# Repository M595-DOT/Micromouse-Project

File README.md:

# Micromouse-Project NGCMAN017 & MDLAYA022

# Description
This project is for the development and design of a MicroMouse for EEE3088F 2025. The Micro Mouse contains a Sensing Module, Power Module, as well as the main control unit(Motherboard). The sensing system will sense obstacles in the proximity of the mouse, while the power module is mainly for powering the motors of the mouse and charging the on-board battery of the mouse.

# Structure
* PCB: The KiCAD Project, Schematics & Layout and Project Libraries
* Firmware: Any software developed for the hardware or instructions on where to find relevant sofware
* Documents: Project documentation and component datasheets
* Production: The gerber files, BOM, Budget, or anything required by the fabrication houses
* Simulation: Any simulation files (eg SPICE) or design stage generated results (E.g matlab or excel)

# Usage
The project documentation can be found in the Documents directory and the files required to produce the PCB can be found in the Production directory.

# Contact
* Manelisi Ngcobo - NGCMAN017@myuct.ac.za
* Ayanda Madlala  -MDLAYA022@myuct.ac.za

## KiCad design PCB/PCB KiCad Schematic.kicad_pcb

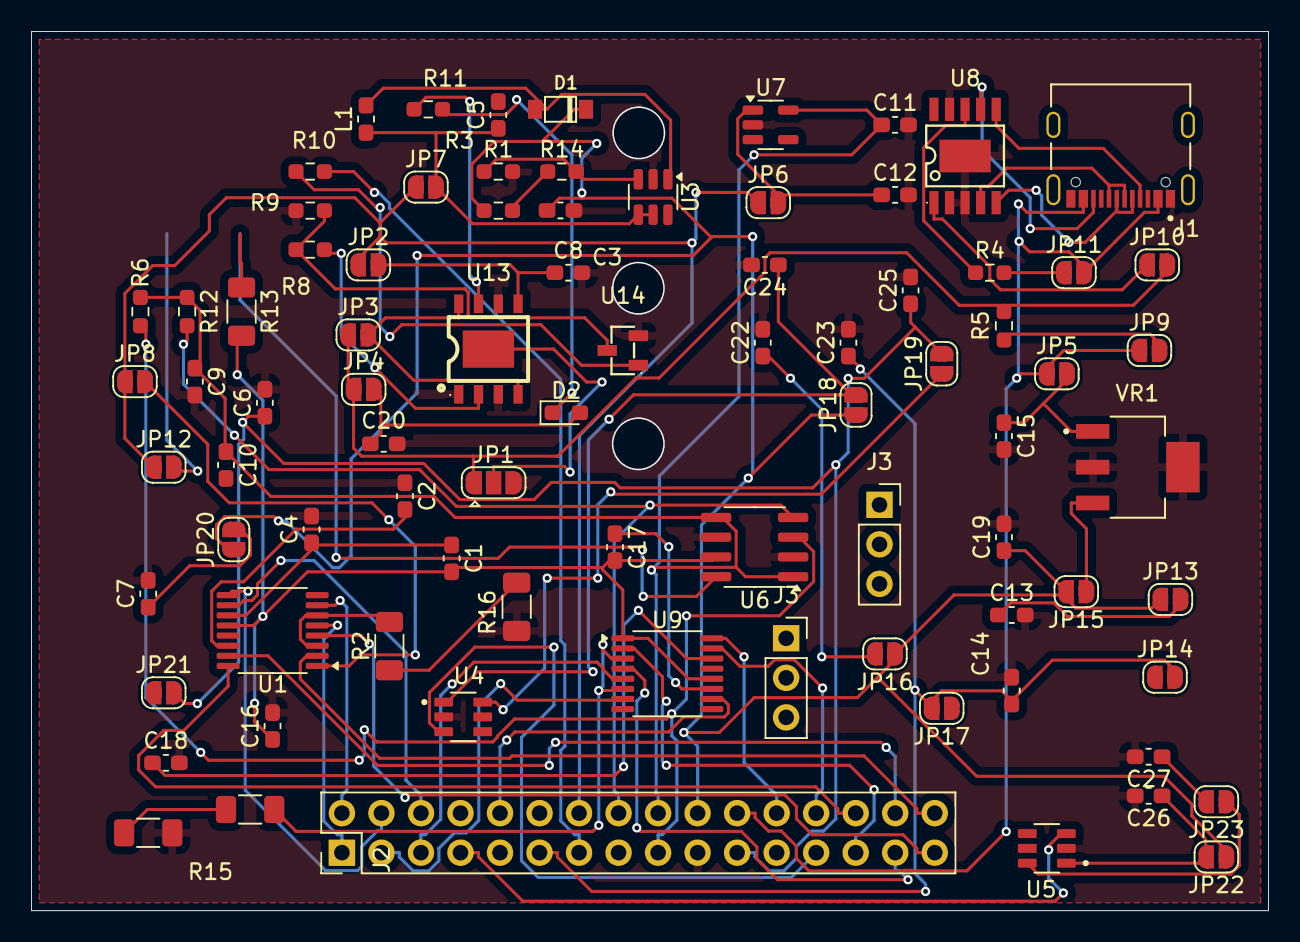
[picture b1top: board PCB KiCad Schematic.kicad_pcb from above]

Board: 2 copper layers, 79.5 x 56.5 mm, 83 parts (0 on the bottom side), 73 nets.

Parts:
C1, C17: 0.01u; C_0603_1608Metric_Pad1.08x0.95mm_HandSolder
C2, C18: 2.2u; C_0603_1608Metric_Pad1.08x0.95mm_HandSolder
C3, C5, C23, C25, C27: 22u; C_0603_1608Metric_Pad1.08x0.95mm_HandSolder
C4, C8, C9, C16, C20: 10u; C_0603_1608Metric_Pad1.08x0.95mm_HandSolder
C6, C10, C14, C19: 0.1u; C_0603_1608Metric_Pad1.08x0.95mm_HandSolder
C7, C11, C12, C13, C22, C24, C26: 1u; C_0603_1608Metric_Pad1.08x0.95mm_HandSolder
C15: 0.22u; C_0603_1608Metric_Pad1.08x0.95mm_HandSolder
D1: SM4007PL-TP; SOD-123FL
D2: LED; LED_0603_1608Metric_Pad1.05x0.95mm_HandSolder
J1: TYPE-C-31-M-12; HRO_TYPE-C-31-M-12
J2: Conn_02x16_Odd_Even; PinHeader_2x16_P2.54mm_Vertical
J3, J3#2: Conn_01x03_Pin; PinSocket_1x03_P2.54mm_Vertical
JP1: Jumper_3_Open; SolderJumper-3_P1.3mm_Open_RoundedPad1.0x1.5mm
JP2, JP3, JP4, JP5, JP6, JP7, JP8, JP9, JP10, JP11, JP12, JP13, JP14, JP15, JP16, JP17, JP18, JP19, JP20, JP21, JP22, JP23: Jumper_2_Open; SolderJumper-2_P1.3mm_Open_RoundedPad1.0x1.5mm
L1: 10u; L_0603_1608Metric_Pad1.05x0.95mm_HandSolder
R1: 15k; R_0603_1608Metric_Pad0.98x0.95mm_HandSolder
R2, R7, R15, R16: 100m; R_1206_3216Metric_Pad1.30x1.75mm_HandSolder
R3: 100k; R_0603_1608Metric_Pad0.98x0.95mm_HandSolder
R4, R14: 10k; R_0603_1608Metric_Pad0.98x0.95mm_HandSolder
R5, R10, R11: 1k; R_0603_1608Metric_Pad0.98x0.95mm_HandSolder
R6, R12: 4.7k; R_0603_1608Metric_Pad0.98x0.95mm_HandSolder
R8: 2k; R_0603_1608Metric_Pad0.98x0.95mm_HandSolder
R9: 3k; R_0603_1608Metric_Pad0.98x0.95mm_HandSolder
R13: 2m; R_1206_3216Metric_Pad1.30x1.75mm_HandSolder
U1, U9: DRV8833PW; TSSOP-16_4.4x5mm_P0.65mm
U3: MT3608; SOT-23-6
U4, U5: TPS22810DBVR; SOT95P280X145-6N
U6: INA219AxD; SOIC-8_3.9x4.9mm_P1.27mm
U7: AP2112K-3.3; SOT-23-5
U8: CH224K; ESSOP-10_L4.9-W3.9-P1.0-LS6.0-TL-EP
U13: TP4056; ESOP-8_L4.9-W3.9-P1.27-LS6.0-BL-EP
U14: MMBT5551_C2145; SOT-23-3_L2.9-W1.3-P1.90-LS2.4-BR
VR1: LM7805MPX_NOPB; VREG_LM7805MPX_NOPB

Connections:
+5V: JP1.1 (A), JP3.1 (A), JP4.1 (A), JP10.2 (B), R5.2
+9V: J1.A4_B9 (VBUS), J1.B4_A9 (VBUS), J2.22, JP5.1 (A), JP9.1 (A), JP11.2 (B)
+BATT: J2.14, JP2.1 (A), JP6.1 (A), JP7.1 (A), JP8.1 (A), JP12.1 (A)
/3V3_OUT: C9.1, C10.1, C11.1, J2.18, R6.1, R12.1, U6.1 (A1), U6.5 (VS), U7.5 (VOUT)
/5V_OUT: C3.1, C19.1, D1.K, J2.20, JP13.1 (A), JP15.2 (B), JP16.1 (A), JP18.1 (A), JP20.1 (A), JP22.1 (A), R3.1
/CC1: J1.A5 (CC1), U8.6 (CC2)
/CC2: J1.B5 (CC2), U8.7 (CC1)
/CHRG: R11.2, U13.7 (CHRG#)
/CTRL_EXT_LOAD1: J2.25, U4.3 (EN/UVLO)
/CTRL_EXT_LOAD2: J2.7, U5.3 (EN/UVLO)
/DM: J1.A7 (DN1), J1.B7 (DN2), U8.5 (DM)
/DP: J1.A6 (DP1), J1.B6 (DP2), U8.4 (DP)
/EXT_LOAD1_OUT: C6.1, C25.1, J2.21, JP19.2 (B), JP21.2 (B)
/EXT_LOAD2_0UT: C14.1, C23.1, J2.11, JP14.2 (B), JP17.2 (B)
/EXT_LOAD2_OUT: C27.1, JP23.2 (B)
/FAST_CHARGE_CTRL: J2.13, R10.1
/I2C1_SCL: J2.16, R12.2, U6.4 (SCL)
/I2C1_SDA: J2.17, R6.2, U6.3 (SDA)
/LOAD: C1.2, C16.1, C17.2, R13.2, U1.12 (VM), U6.7 (IN-), U9.1 (~SLEEP), U9.12 (VM)
/MOTOR1_CTRL1: J2.28, U1.16 (AIN1)
/MOTOR1_CTRL2: J2.30, U1.15 (AIN2)
/MOTOR2_CTRL1: J2.4, U1.9 (BIN1)
/MOTOR2_CTRL2: J2.6, U1.10 (BIN2)
/MOTOR3_CTRL1: J2.24, U9.16 (AIN1)
/MOTOR3_CTRL2: J2.26, U9.15 (AIN2)
/MOTOR4_CTRL1: J2.8, U9.9 (BIN1)
/MOTOR4_CTRL2: J2.10, U9.10 (BIN2)
/Motor1_A_OUT: J2.32, U1.2 (AOUT1)
/Motor1_B_OUT: J2.31, U1.4 (AOUT2)
/Motor2_A_OUT: J2.2, U1.7 (BOUT1)
/Motor2_B_OUT: J2.1, U1.5 (BOUT2)
/Motor3_A_OUT: J2.27, U9.2 (AOUT1)
/Motor3_B_OUT: J2.29, U9.4 (AOUT2)
/Motor4_A_OUT: J2.3, U9.7 (BOUT1)
/Motor4_B_OUT: J2.5, U9.5 (BOUT2)
/PROG: R8.1, U13.2 (PROG)
GND: C2.1, C3.2, C4.2, C5.2, C6.2, C7.2, C8.2, C9.2, C10.2, C11.2, C12.2, C13.2, C14.2, C15.2, C16.2, C18.2, C19.2, C20.2, C22.2, C23.2, C24.2, C25.2, C26.2, C27.2, J1.A1_B12 (GND), J1.B1_A12 (GND), J2.19, J2.23, JP1.3 (B), R1.2, R9.2, R15.1, R16.1, U1.13 (GND), U3.2 (GND), U4.2 (GND), U5.2 (GND), U6.2 (A0), U6.6 (GND), U7.2 (GND), U8.2 (CFG2), U8.3 (CFG3), U8.9 (CFG1), U8.11 (GND), U9.13 (GND), U13.1 (TEMP), U13.3 (GND), U13.6 (STDBY#), U14.2 (E), VR1.2 (GND_2), VR1.4 (GND_4)
unnamed: C20.1, D2.2 (A), JP4.2 (B)
unnamed: D2.1 (K), R11.1
unnamed: J3.1, J3#2.1, R13.1, U6.8 (IN+)
unnamed: J3.2, J3#2.2, JP12.2 (B)
unnamed: JP1.2 (C), U13.9 (EP)
unnamed: C8.1, JP2.2 (B), U13.5 (BAT)
unnamed: JP3.2 (B), U13.4 (VCC), U13.8 (CE)
unnamed: C15.1, JP5.2 (B), VR1.1 (INPUT)
unnamed: C12.1, JP6.2 (B), U7.1 (VIN)
unnamed: C5.1, JP7.2 (B), L1.1, U3.4 (EN), U3.5 (IN)
unnamed: JP8.2 (B), U1.1 (~SLEEP)
unnamed: JP9.2 (B), R5.1
unnamed: JP10.1 (A), U8.1 (VDD)
unnamed: JP11.1 (A), R4.2
unnamed: C13.1, JP13.2 (B)
unnamed: JP15.1 (A), VR1.3 (OUTPUT)
unnamed: C22.1, JP16.2 (B)
unnamed: C24.1, JP18.2 (B), U4.1 (VIN)
unnamed: JP19.1 (A), U4.6 (VOUT)
unnamed: C7.1, JP20.2 (B)
unnamed: C26.1, JP22.2 (B), U5.1 (VIN)
unnamed: JP23.1 (A), U5.6 (VOUT)
unnamed: R3.2, R14.1
unnamed: R7.1, R15.2
unnamed: R2.1, R16.2
unnamed: R2.2, U1.3 (AISEN), U1.6 (BISEN)
unnamed: C1.1, C4.1, U1.11 (VCP)
unnamed: C2.2, U1.14 (VINT)
unnamed: R1.1, R14.2, U3.3 (FB)
unnamed: D1.A, L1.2, U3.1 (SW)
unnamed: R4.1, U8.8 (VBUS)
unnamed: R7.2, U9.3 (AISEN), U9.6 (BISEN)
unnamed: C17.1, U9.11 (VCP)
unnamed: C18.1, U9.14 (VINT)
unnamed: R10.2, U14.1 (B)
unnamed: R8.2, R9.1, U14.3 (C)

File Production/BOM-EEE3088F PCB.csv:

Comment,Designator,Footprint,LCSC,Quantity
10u,"C16,C4,L1",C_0603_1608Metric_Pad1.08x0.95mm_HandSolder,C1035,3
INA219AxD,U6,SOIC-8_3.9x4.9mm_P1.27mm,C138706,1
1u,"C11,C12,C13,C22,C24,C26,C7",C_0603_1608Metric_Pad1.08x0.95mm_HandSolder,C15849,7
TP4056,U13,ESOP-8_L4.9-W3.9-P1.27-LS6.0-BL-EP,C16581,1
TYPE-C-31-M-12,J1,HRO_TYPE-C-31-M-12,C165948,1
MT3608,U3,SOT-23-6,C19189893,1
10u,"C20,C8,C9",C_0603_1608Metric_Pad1.08x0.95mm_HandSolder,C19702,3
TPS22810DBVR,"U4,U5",SOT95P280X145-6N,C205990,2
0.22u,C15,C_0603_1608Metric_Pad1.08x0.95mm_HandSolder,C21120,1
1k,"R10,R11,R5",R_0603_1608Metric_Pad0.98x0.95mm_HandSolder,C21190,3
MMBT5551_C2145,U14,SOT-23-3_L2.9-W1.3-P1.90-LS2.4-BR,C2145,1
15k,R1,R_0603_1608Metric_Pad0.98x0.95mm_HandSolder,C22809,1
LED,D2,LED_0603_1608Metric_Pad1.05x0.95mm_HandSolder,C2286,1
2k,R8,R_0603_1608Metric_Pad0.98x0.95mm_HandSolder,C22975,1
4.7k,"R12,R6",R_0603_1608Metric_Pad0.98x0.95mm_HandSolder,C23162,2
AP2112K-3.3,U7,SOT-23-5,C23380830,1
2.2u,"C18,C2",C_0603_1608Metric_Pad1.08x0.95mm_HandSolder,C23630,2
100m,"R15,R16,R2,R7",R_1206_3216Metric_Pad1.30x1.75mm_HandSolder,C25334,4
100k,R3,R_0603_1608Metric_Pad0.98x0.95mm_HandSolder,C25803,1
10k,"R14,R4",R_0603_1608Metric_Pad0.98x0.95mm_HandSolder,C25804,2
LM7805MPX_NOPB,VR1,VREG_LM7805MPX_NOPB,C2848241,1
2m,R13,R_1206_3216Metric_Pad1.30x1.75mm_HandSolder,C2994640,1
3k,R9,R_0603_1608Metric_Pad0.98x0.95mm_HandSolder,C4211,1
DRV8833PW,"U1,U9",TSSOP-16_4.4x5mm_P0.65mm,C50506,2
0.01u,"C1,C17",C_0603_1608Metric_Pad1.08x0.95mm_HandSolder,C57112,2
22u,"C23,C25,C27,C3,C5",C_0603_1608Metric_Pad1.08x0.95mm_HandSolder,C59461,5
SM4007PL-TP,D1,SOD-123FL,C64898,1
0.1u,"C10,C14,C19,C6",C_0603_1608Metric_Pad1.08x0.95mm_HandSolder,C84772,4
CH224K,U8,ESSOP-10_L4.9-W3.9-P1.0-LS6.0-TL-EP,C970725,1

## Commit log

2025-05-10 Create Power Module
2025-05-10 Create PCB
